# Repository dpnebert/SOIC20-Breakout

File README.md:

# SOIC20-Breakout

The need to prototype using a SOIC-20 uC had me create this little gem.

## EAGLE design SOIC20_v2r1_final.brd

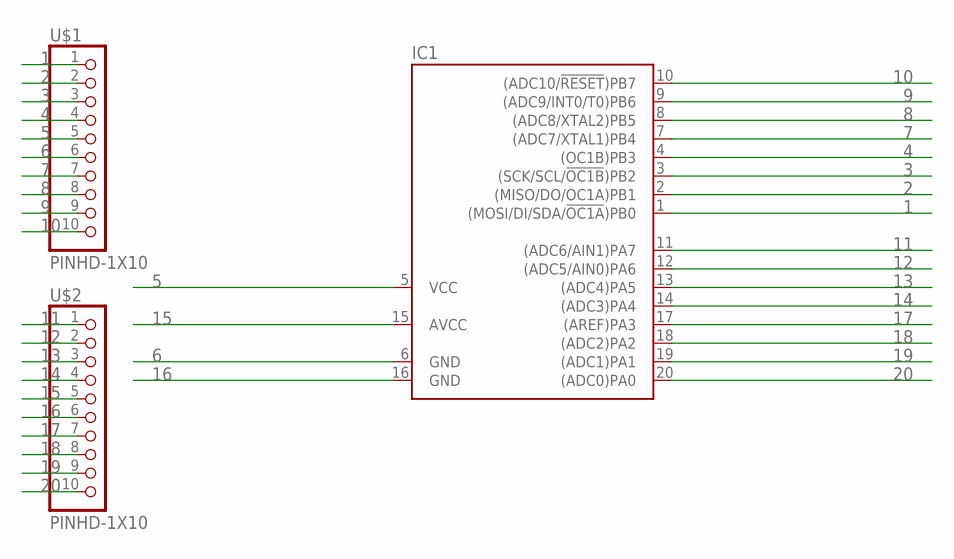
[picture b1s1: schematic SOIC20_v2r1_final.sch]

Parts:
IC1: TINY26LS; SO20L
U$1, U$2: PINHD-1X10; 1X10-BIG

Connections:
1: IC1.1 ((MOSI/DI/SDA/!OC1A!)PB0), U$1.1
2: IC1.2 ((MISO/DO/OC1A)PB1), U$1.2
3: IC1.3 ((SCK/SCL/!OC1B!)PB2), U$1.3
4: IC1.4 ((OC1B)PB3), U$1.4
5: IC1.5 (VCC), U$1.5
6: IC1.6 (GND), U$1.6
7: IC1.7 ((ADC7/XTAL1)PB4), U$1.7
8: IC1.8 ((ADC8/XTAL2)PB5), U$1.8
9: IC1.9 ((ADC9/INT0/T0)PB6), U$1.9
10: IC1.10 ((ADC10/!RESET!)PB7), U$1.10
11: IC1.11 ((ADC6/AIN1)PA7), U$2.1
12: IC1.12 ((ADC5/AIN0)PA6), U$2.2
13: IC1.13 ((ADC4)PA5), U$2.3
14: IC1.14 ((ADC3)PA4), U$2.4
15: IC1.15 (AVCC), U$2.5
16: IC1.16 (GND), U$2.6
17: IC1.17 ((AREF)PA3), U$2.7
18: IC1.18 ((ADC2)PA2), U$2.8
19: IC1.19 ((ADC1)PA1), U$2.9
20: IC1.20 ((ADC0)PA0), U$2.10

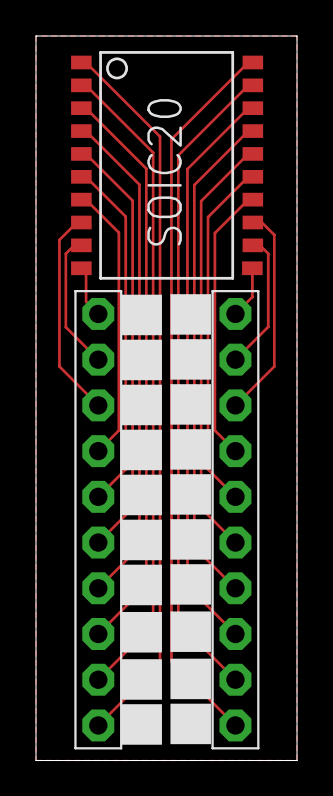
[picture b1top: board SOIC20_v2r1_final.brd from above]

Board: 2 copper layers, 14.5 x 40.2 mm, 3 parts (0 on the bottom side), 20 nets.

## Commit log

2019-12-04 Create newfiles.stupidWayToCreateNewDirectory
    nope
